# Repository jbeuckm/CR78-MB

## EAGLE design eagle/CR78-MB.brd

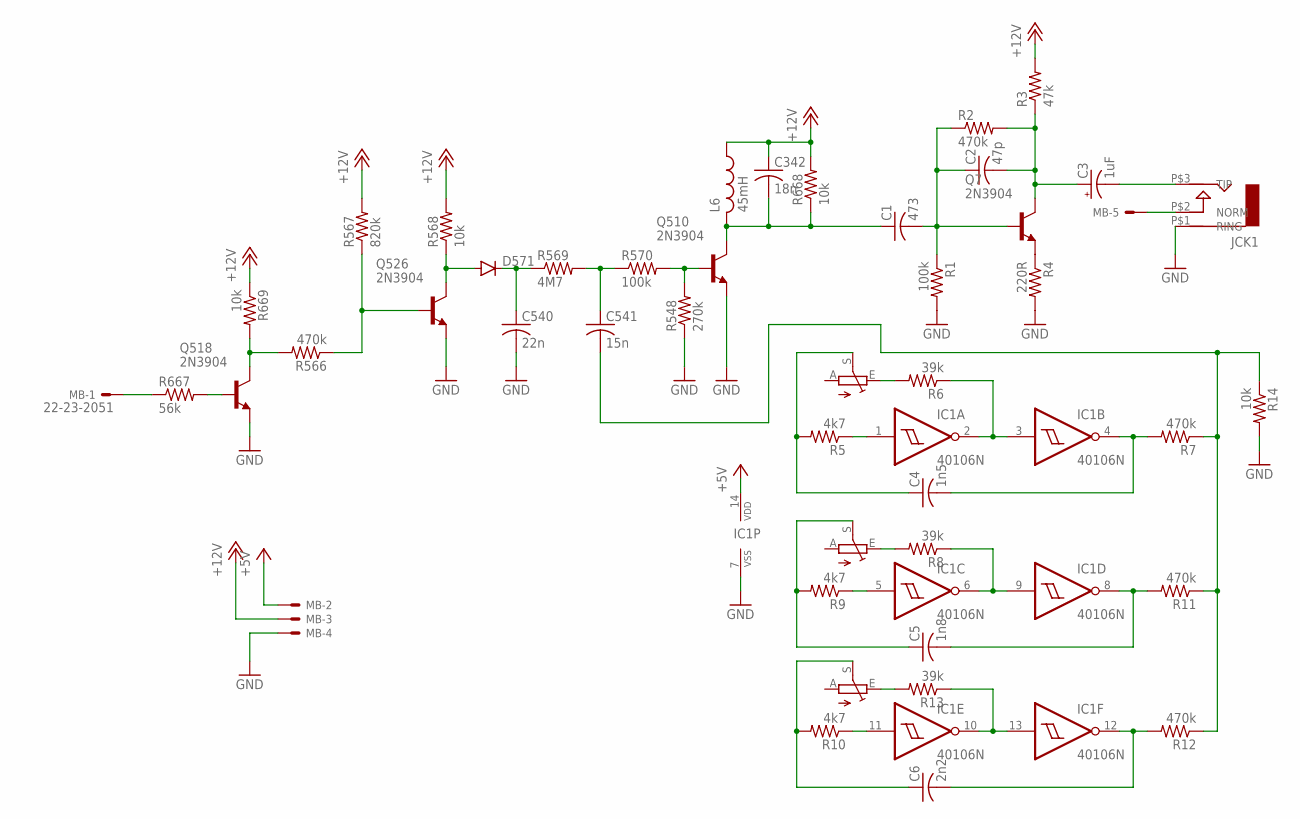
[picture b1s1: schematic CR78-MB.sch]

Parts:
C1: 473; C050-025X075
C2: 47p; C025-030X050
C3: 1uF; B45181B
C4: 1n5; C050-025X075
C5: 1n8; C050-025X075
C6: 2n2; C050-025X075
C342: 18n; C050-025X075
C540: 22n; C050-025X075
C541: 15n; C050-025X075
D571: DIODE1N4148; DIODE-1N4148
IC1: 40106N; DIL14
JCK1: AUDIO-JACK; ERTHENVAR-JACK-90DEG
L6: 45mH; 0204/5
MB: 22-23-2051
Q7, Q510, Q518, Q526: 2N3904; TO92
R1, R570: 100k; 0207/7
R2, R7, R11, R12, R566: 470k; 0207/7
R3: 47k; 0207/7
R4: 220R; 0207/7
R5, R9, R10: 4k7; 0207/7
R6, R8, R13: 39k; 0207/7
R14, R568, R668, R669: 10k; 0207/7
R548: 270k; 0207/7
R567: 820k; 0207/7
R569: 4M7; 0207/7
R667: 56k; 0207/7
VR1, VR2, VR3: 20K; B64Y

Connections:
+5V: IC1.14 (VDD), MB.2
+12V: C342.1, L6.1, MB.3, R3.2, R567.2, R568.2, R668.2, R669.1
GND: C540.2, IC1.7 (VSS), JCK1.P$1 (RING), MB.4, Q510.3 (E), Q518.3 (E), Q526.3 (E), R1.2, R4.2, R14.2, R548.1
unnamed: D571.A, Q526.1 (C), R568.1
unnamed: Q526.2 (B), R566.1, R567.1
unnamed: C541.2, R7.1, R11.1, R12.1, R14.1
unnamed: C540.1, D571.C, R569.1
unnamed: IC1.2 (O), IC1.3 (I), R6.1
unnamed: IC1.6 (O), IC1.9 (I), R8.1
unnamed: JCK1.P$2 (NORM), MB.5
unnamed: IC1.5 (I), R9.1
unnamed: IC1.11 (I), R10.1
unnamed: IC1.10 (O), IC1.13 (I), R13.1
unnamed: C5.2, IC1.8 (O), R11.2
unnamed: C541.1, R569.2, R570.1
unnamed: Q510.2 (B), R548.2, R570.2
unnamed: C6.2, IC1.12 (O), R12.2
unnamed: Q7.3 (E), R4.1
unnamed: C2.2, C3.+, Q7.1 (C), R2.2, R3.1
unnamed: IC1.1 (I), R5.1
unnamed: C1.2, C2.1, Q7.2 (B), R1.1, R2.1
unnamed: C3.-, JCK1.P$3 (TIP)
unnamed: Q518.1 (C), R566.2, R669.2
unnamed: Q518.2 (B), R667.2
unnamed: C4.2, IC1.4 (O), R7.2
unnamed: R6.2, VR1.E
unnamed: MB.1, R667.1
unnamed: R8.2, VR2.E
unnamed: R13.2, VR3.E
unnamed: C1.1, C342.2, L6.2, Q510.1 (C), R668.1
unnamed: C4.1, R5.2, VR1.S
unnamed: C5.1, R9.2, VR2.S
unnamed: C6.1, R10.2, VR3.S

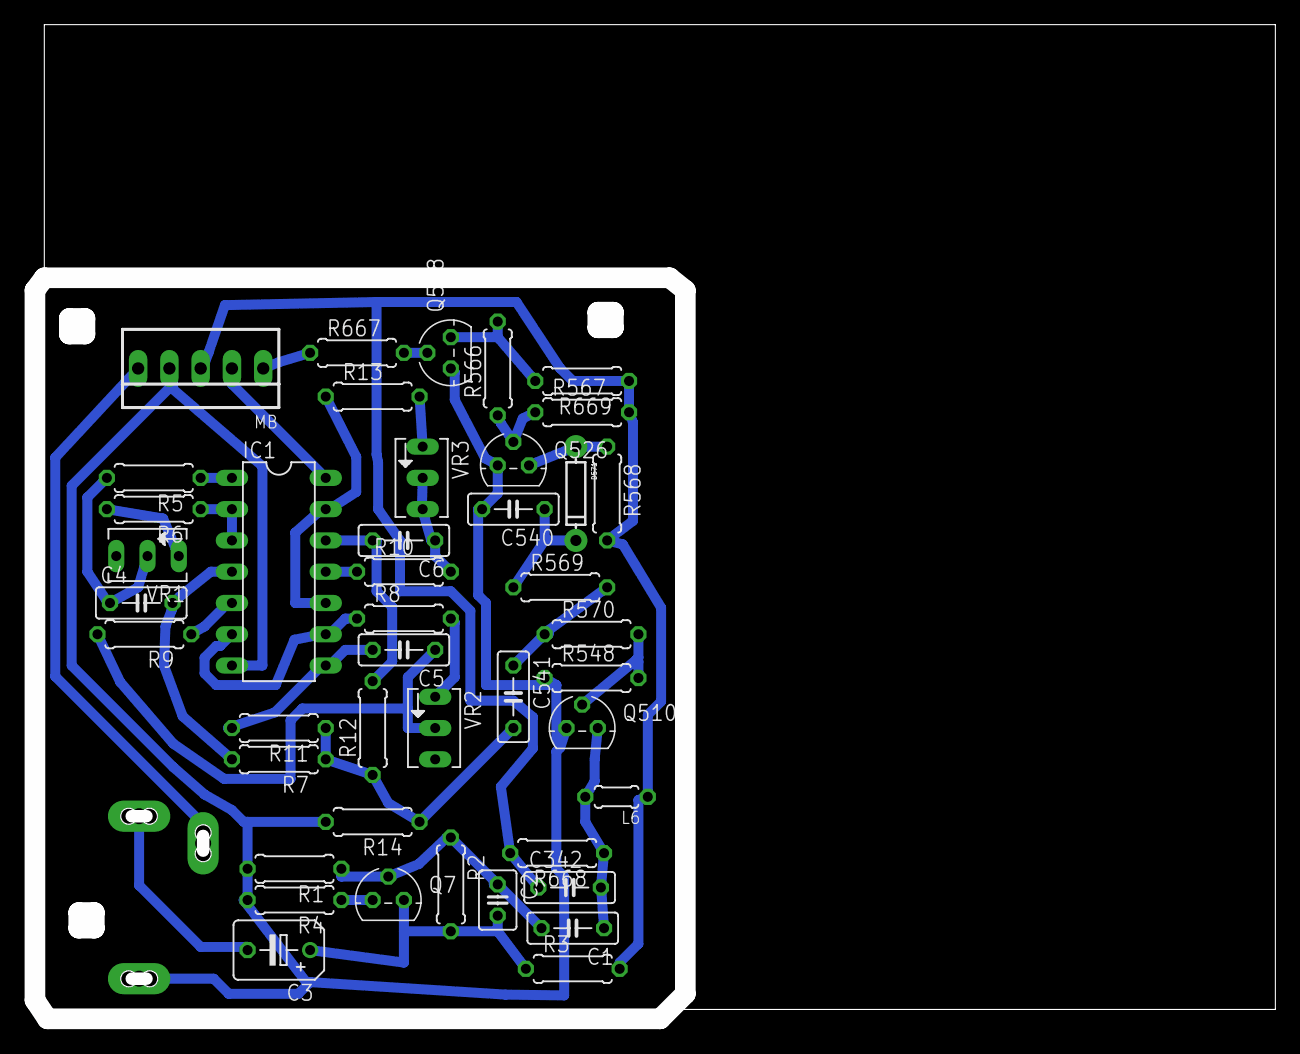
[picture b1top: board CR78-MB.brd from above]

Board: 2 copper layers, 99.9 x 79.9 mm, 44 parts (0 on the bottom side), 33 nets.

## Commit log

2016-06-16 initial from GU
2016-06-17 half schemo
2016-06-17 schemo
2016-06-17 starting brd
2016-06-17 parts on the brd
2016-06-17 96pct auto
2016-06-17 routed
2016-06-17 cutout
2016-06-17 moved to corner
2016-06-18 pro file

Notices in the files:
parts and their libraries:
SparkFun-DiscreteSemi: Licensing: Creative Commons ShareAlike 4.0 International - https://creativecommons.org/licenses/by-sa/4.0
